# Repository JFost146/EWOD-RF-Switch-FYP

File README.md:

# Final Year Project  
## MEng Electrical and Electronic Engineering  
### Jack Foster — University of Birmingham

This repository contains the work completed for my final year MEng project at the University of Birmingham.

The project focuses on the development of an **electrowetting-on-dielectric (EWOD) circuit** designed to actuate a liquid droplet into a waveguide channel, where the liquid acts as part of an **RF switch**.

---

## Licence

This project is released under the **GNU General Public License v3.0**.

You are free to use, modify, and distribute the software and associated project files under the terms of the GPLv3. Any redistributed or modified versions must also comply with the GPLv3 terms.

A full copy of the licence is provided in the [`LICENSE`](license.txt) file.

Parts of this project are derived from or inspired by the GaudiLabs OpenDrop project and Nick de Smith’s Nixie high-voltage switching PSU. Please refer to the acknowledgements section for the original sources.

---

## Project Overview

The repository includes:

- KiCad circuit schematics and PCB design files
- Electrode board designs for EWOD testing
- Arduino-based control software
- RF switch simulation and measurement results
- Supporting notes and design references

---

## Circuit Basics

The `Circuit` folder contains the **KiCad 9.0** schematics, footprints, and manufacturing files used for the PCB.

The boards used in the project were manufactured by **JLCPCB** at approximately **£30 per board**. These boards used **ENIG plating** to optimise coupling between electrodes for EWOD operation. However, the design would likely still work with the cheaper **HASL** finish.

---

## Microcontroller and Software

The circuit was tested using a **Seeed Studio XIAO nRF52840**:

[Seeed Studio XIAO nRF52840 Documentation](https://wiki.seeedstudio.com/XIAO_BLE/)

The board should also be compatible with other microcontroller boards, as the controllable components operate using:

- `3V3`
- Clock signal
- Latch / chip-select signal

The controllable components are:

- Digital potentiometer
- High-voltage switch controller

The control code is written for **Arduino** and can be found in the `Software` folder.

---

## Board Setup and EWOD Testing

To use the board:

1. Snap off the electrode boards.
2. Solder all required components.
3. Connect an electrode board using fly-wires.
4. Add a hydrophobic oil layer to the electrodes.  
   - Silicone oil, **5 cSt**, is preferred.
5. Place a dielectric layer on top of the oil.  
   - Cling film can be used.
6. Add another oil layer on top of the dielectric.
7. Place the droplet above an electrode.
8. Observe the EWOD actuation.

---

## Notes and Testing Observations

- The potentiometer can be bypassed using the `R_pot_sub` resistor pads with either:
  - a `0 Ω` resistor, or
  - a solder bridge.

- Successful tests were proven at maximum voltage output, with the potentiometer set to `0 Ω`.

- EWOD actuation is likely to work at voltages of **200 V or higher**.

- The best EWOD results were achieved using the rectangular electrodes with droplets whose diameter was approximately equal to, or larger than, the width of one electrode.

- The board design is derived from the GaudiLabs OpenDrop board:  
  [GaudiLabs OpenDrop](https://www.gaudi.ch/OpenDrop/)

- The DC-DC converter design originates from Nick de Smith’s Nixie high-voltage switching PSU:  
  [Nick de Smith Nixie PSU](https://www.nick.desmith.net/Electronics/NixiePSU.html)

---

## Board Specifications

| Parameter | Value |
|---|---|
| Input voltage | 5 V |
| Input current at maximum output | 0.16 A |
| Theoretical input range | 4.5 V to 16 V |
| Electrode output voltage range | 50 V to 290 V |
| Electrode output current range | 2.3 µA to 13.2 µA |
| Number of electrode designs | 7 |
| Minimum tested standalone output from XIAO nRF52840 USB input  | 50 V |

---

## RF Switch Investigation

The `Liquid Switch Tests` results contain:

- CST simulation results
- VNA measurement results
- RF switch response data for different liquids

These results investigate the behaviour of an RF switch when closed using various liquid materials.

---

## Switch Link

Add switch link here.

---

## Acknowledgements

This project builds on open-source and publicly documented work from:

- [GaudiLabs OpenDrop](https://www.gaudi.ch/OpenDrop/)
- [Nick de Smith’s Nixie HV Switching PSU](https://www.nick.desmith.net/Electronics/NixiePSU.html)

---

## Author

**Jack Foster**  
MEng Electrical and Electronic Engineering  
University of Birmingham

## Project Supervisor

**Prof. Yi Wang**  
Department of Electronic, Electrical and Systems Engineering  
University of Birmingham

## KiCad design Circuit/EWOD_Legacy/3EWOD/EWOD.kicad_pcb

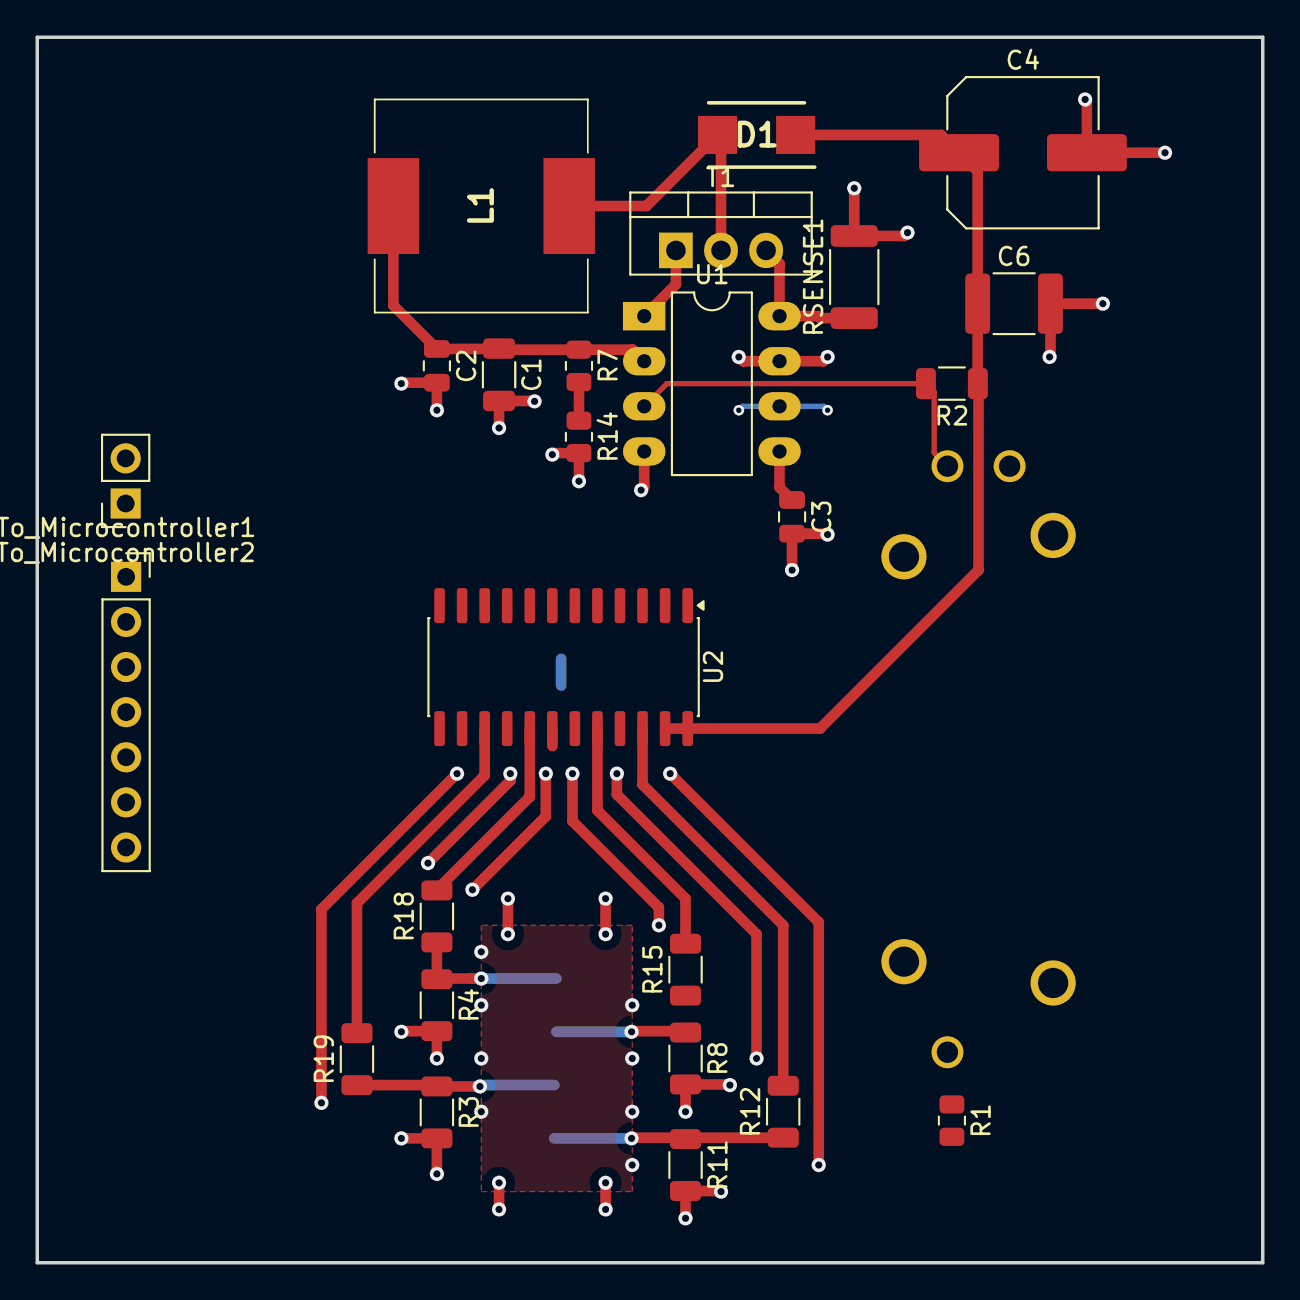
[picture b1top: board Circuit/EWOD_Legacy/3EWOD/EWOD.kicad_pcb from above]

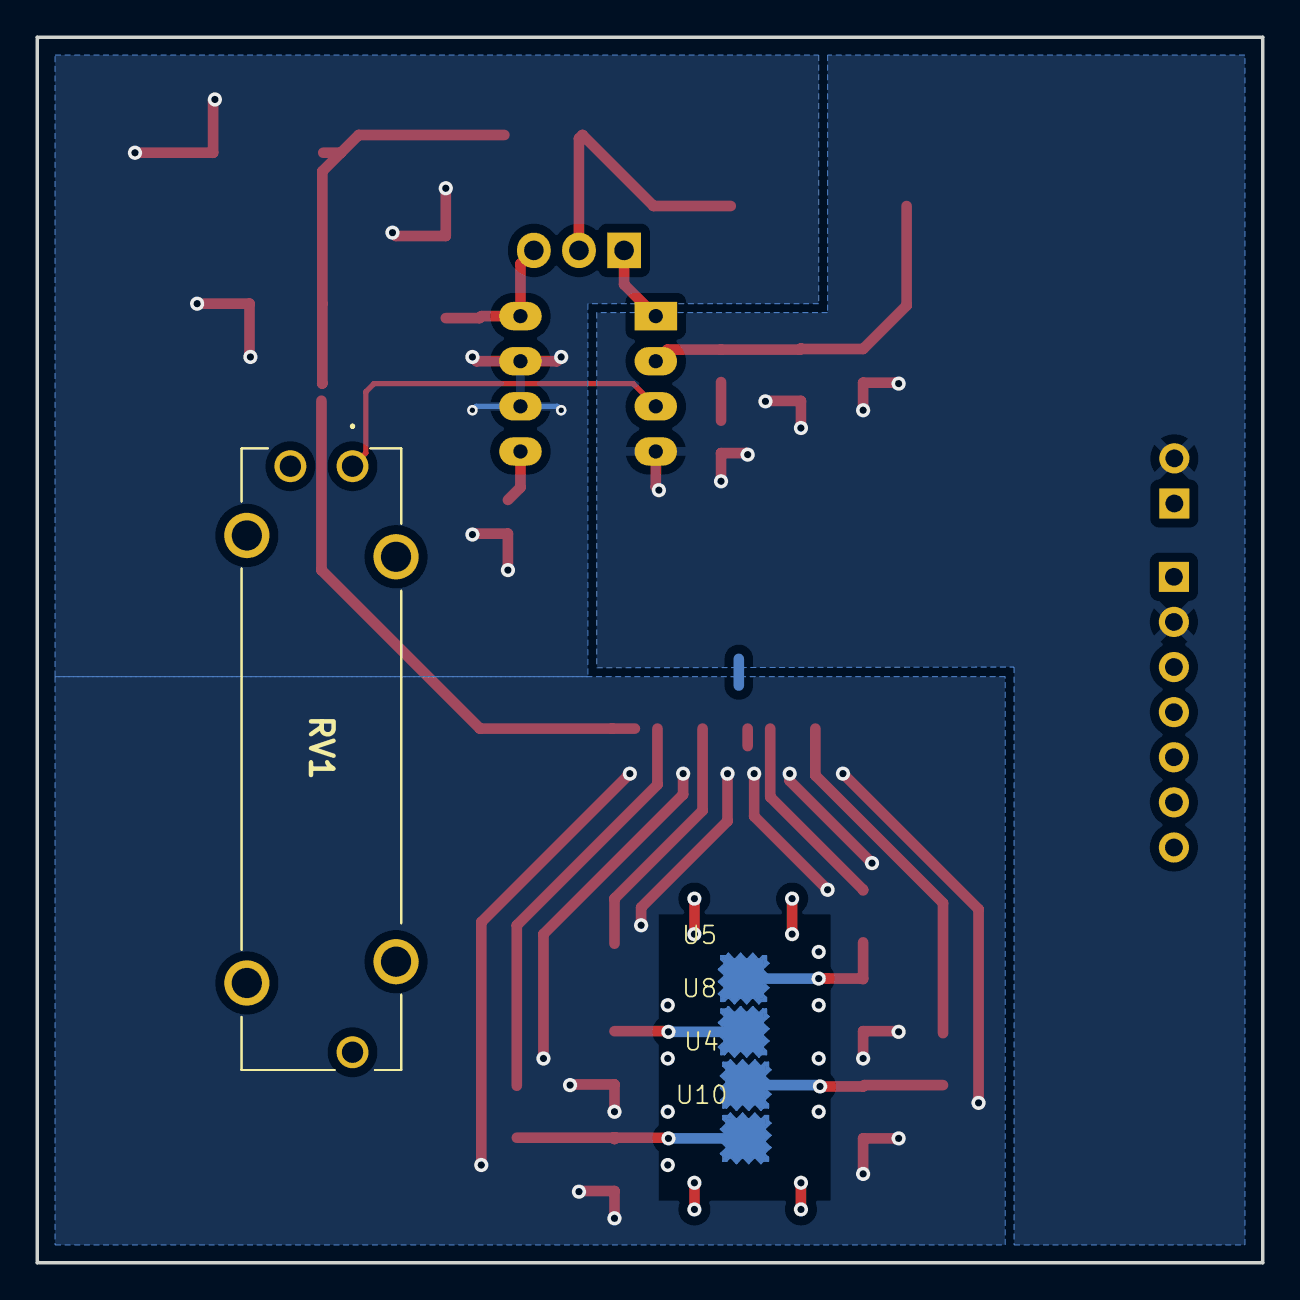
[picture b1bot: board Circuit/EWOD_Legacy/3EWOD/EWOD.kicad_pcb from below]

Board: 2 copper layers, 69.0 x 69.0 mm, 30 parts (5 on the bottom side), 24 nets.

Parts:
C1: 100uF, 6.3V; C_1206_3216Metric
C2, C3: 100nF; C_0805_2012Metric
C4: 4u7, 250V; C_Elec_8x10.2
C6: 100nF, 250V; C_1812_4532Metric
D1: ES2F; DIOM5436X244N
L1: 100uH; CDRH125101MC
R1: ak; R_0805_2012Metric
R2: 1M5; R_1206_3216Metric
R3, R4, R8, R11: 22M; R_1206_3216Metric
R7: 6.8k; R_0805_2012Metric
R12, R15, R18, R19: 200; R_1206_3216Metric
R14: 10k; R_0805_2012Metric
RSENSE1: 0R1; R_2010_5025Metric
RV1: R_Potentiometer; PTA20432015CPB503
T1: TK560P60Y; TO-220-3_Vertical
To_Microcontroller1: Conn_01x07; PinSocket_1x07_P2.54mm_Vertical
To_Microcontroller2: Conn_01x07; PinSocket_1x02_P2.54mm_Vertical
U1: MAX1771ESA; PowerIntegrations_PDIP-8
U2: HV513; SO-24_5.3x15mm_P1.27mm
U4: Electrode 2; Electrode
U5: Electrode 3; Electrode
U8: Electrode 6; Electrode
U10: Electrode 8; Electrode

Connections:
GND: C1.2, C2.2, C3.2, C4.2, C6.2, R1.2, R3.2, R4.2, R8.2, R11.2, R14.2, RSENSE1.2, To_Microcontroller1.2, To_Microcontroller2.2, U1.4 (SHDN), U1.6 (AGND), U1.7 (GND), U2.11 (LVGND), U2.13 (HVGND), U2.14 (HVGND)
unnamed: R1.1, RV1.3
unnamed: R11.1, R12.1, U10.1
unnamed: R8.1, R15.1, U8.1
unnamed: R4.1, R18.1, U5.1
unnamed: R3.1, R19.1, U4.1
unnamed: D1.2, L1.2, T1.2 (D)
unnamed: T1.1 (G), U1.1 (EXT)
unnamed: RSENSE1.1, T1.3 (S), U1.8 (CS)
unnamed: To_Microcontroller1.1, U2.2 (VDD_logic_supply)
unnamed: To_Microcontroller1.3, U2.4 (BL)
unnamed: To_Microcontroller1.4, U2.5 (POL)
unnamed: To_Microcontroller1.5, U2.6 (CLK)
unnamed: To_Microcontroller1.6, U2.7 (LE)
unnamed: To_Microcontroller1.7, U2.10 (DIN)
unnamed: R2.2, RV1.1, U1.3 (FB)
unnamed: C3.1, U1.5 (REF)
unnamed: C1.1, C2.1, L1.1, R7.1, U1.2 (VCC)
unnamed: R19.2, U2.15 (HVOUT1)
unnamed: R18.2, U2.17 (HVOUT3)
unnamed: R15.2, U2.20 (HVOUT6)
unnamed: R12.2, U2.22 (HVOUT8)
V_HV: C4.1, C6.1, D1.1, R2.1, U2.23 (HVpp), U2.24 (HVpp)
V_In_SENS: R7.2, R14.1

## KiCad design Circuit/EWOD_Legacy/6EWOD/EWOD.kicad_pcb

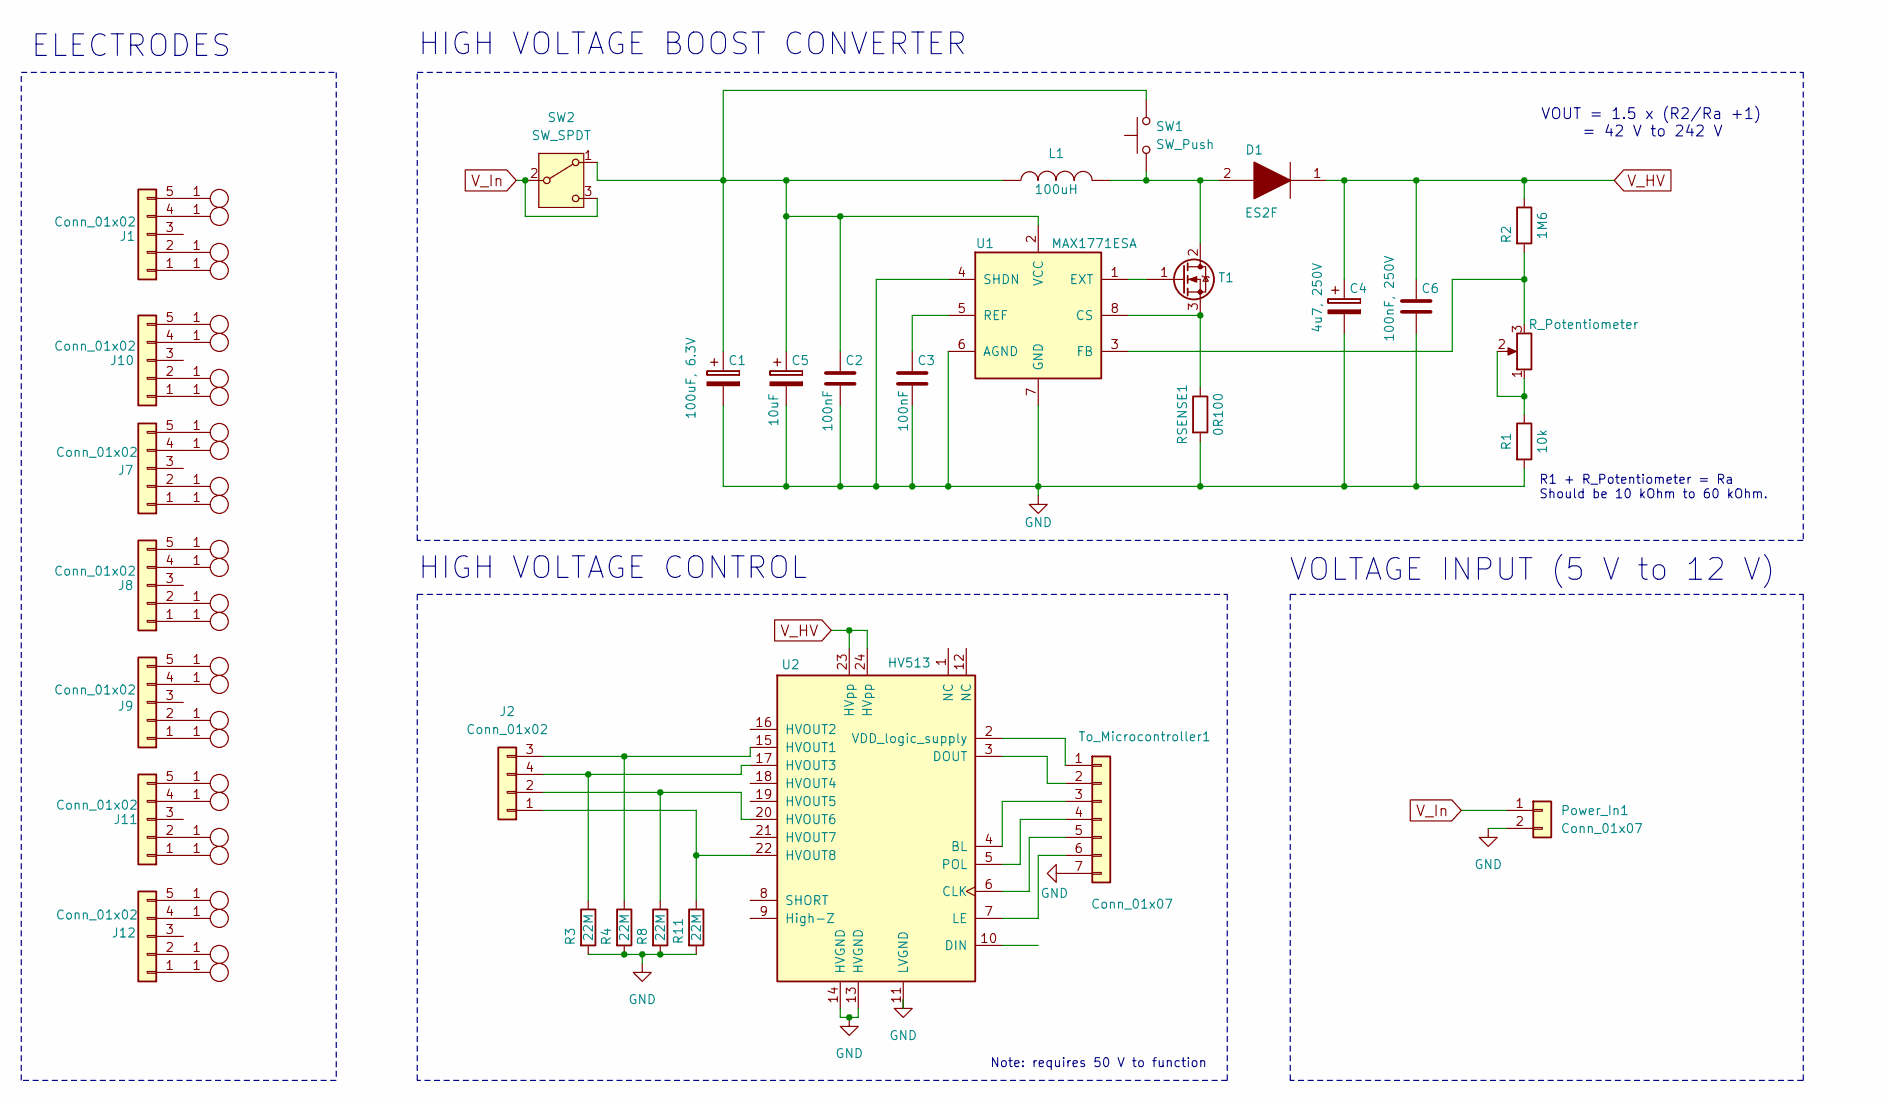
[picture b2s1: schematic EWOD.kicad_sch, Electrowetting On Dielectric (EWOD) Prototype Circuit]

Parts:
C1: 100uF, 6.3V; CP_Elec_6.3x5.4_Nichicon
C2, C3: 100nF; C_0805_2012Metric
C4: 4u7, 250V; CP_Elec_10x10.5
C5: 10uF; C_1206_3216Metric
C6: 100nF, 250V; C_1812_4532Metric
D1: ES2F; DIOM5436X244N; Manufacturer_Part_Number ES2F-E3/52T; Mouser Part Number 625-ES2F-E3
J1, J7, J8, J9, J10, J11, J12: Conn_01x02; Zhaoxing_VH_ZX-VH3.96-5PLT_1x05-1MP_P3.96mm_Vertical_0
J2: Conn_01x02; PinSocket_1x04_P2.54mm_Vertical
L1: 100uH; CDRH125101MC
Power_In1: Conn_01x07; PinSocket_1x02_P2.54mm_Vertical
R1: 10k; R_0805_2012Metric
R2: 1M6; R_1206_3216Metric
R3, R4, R8, R11: 22M; R_1206_3216Metric
RSENSE1: 0R100; R_2010_5025Metric
RV1: R_Potentiometer; SOT-363_SC-70-6_Handsoldering
SW1: SW_Push
SW2: SW_SPDT; PinHeader_1x03_P2.54mm_Vertical
T1: TK560P60Y; TO-220-3_Vertical
To_Microcontroller1: Conn_01x07; PinSocket_1x07_P2.54mm_Vertical
U1: MAX1771ESA; PowerIntegrations_PDIP-8
U2: HV513; SOP-24_7.5x15.4mm_P1.27mm
U4: Electrode 2; Electrode
U5: Electrode 3; Electrode
U8: Electrode 6; Electrode
U10: Electrode 8; Electrode
U11, U12, U13, U14: Electrode 2; Electrode_2_1
U15, U16, U17, U18: Electrode 2; Electrode_3
U19, U20, U21, U22: Electrode 2; Electrode_4
U23, U24, U25, U26: Electrode 2; Electrode_2
U27, U28, U29, U30: Electrode 2; Electrode_5
U31, U32, U33, U34: Electrode 2; Electrode_6

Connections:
GND: C1.2, C2.2, C3.2, C4.2, C5.2, C6.2, Power_In1.2, R1.2, R3.2, R4.2, R8.2, R11.2, RSENSE1.2, To_Microcontroller1.7, U1.4 (SHDN), U1.6 (AGND), U1.7 (GND), U2.11 (LVGND), U2.13 (HVGND), U2.14 (HVGND)
unnamed: J1.1, U10.1
unnamed: J1.2, U8.1
unnamed: J1.4, U5.1
unnamed: J1.5, U4.1
unnamed: J2.1, R11.1, U2.22 (HVOUT8)
unnamed: J2.2, R8.1, U2.20 (HVOUT6)
unnamed: J2.4 (Pin_3), R3.1, U2.17 (HVOUT3)
unnamed: J2.3 (Pin_4), R4.1, U2.15 (HVOUT1)
unnamed: J7.1, U14.1
unnamed: J7.2, U13.1
unnamed: J7.4, U12.1
unnamed: J7.5, U11.1
unnamed: J8.1, U18.1
unnamed: J8.2, U17.1
unnamed: J8.4, U16.1
unnamed: J8.5, U15.1
unnamed: J9.1, U22.1
unnamed: J9.2, U21.1
unnamed: J9.4, U20.1
unnamed: J9.5, U19.1
unnamed: J10.1, U26.1
unnamed: J10.2, U25.1
unnamed: J10.4, U24.1
unnamed: J10.5, U23.1
unnamed: J11.1, U30.1
unnamed: J11.2, U29.1
unnamed: J11.4, U28.1
unnamed: J11.5, U27.1
unnamed: J12.1, U34.1
unnamed: J12.2, U33.1
unnamed: J12.4, U32.1
unnamed: J12.5, U31.1
unnamed: R1.1, RV1.1, RV1.2
unnamed: C1.1, C2.1, C5.1, L1.1, SW1.2, SW2.1 (A), U1.2 (VCC)
unnamed: D1.2, L1.2, SW1.1, T1.2 (D)
unnamed: T1.1 (G), U1.1 (EXT)
unnamed: RSENSE1.1, T1.3 (S), U1.8 (CS)
unnamed: To_Microcontroller1.1, U2.2 (VDD_logic_supply)
unnamed: To_Microcontroller1.2, U2.3 (DOUT)
unnamed: To_Microcontroller1.3, U2.4 (BL)
unnamed: To_Microcontroller1.4, U2.5 (POL)
unnamed: To_Microcontroller1.5, U2.6 (CLK)
unnamed: To_Microcontroller1.6, U2.7 (LE)
unnamed: R2.2, RV1.3, U1.3 (FB)
unnamed: C3.1, U1.5 (REF)
V_HV: C4.1, C6.1, D1.1, R2.1, U2.23 (HVpp), U2.24 (HVpp)
V_In: Power_In1.1, SW2.2 (B), SW2.3 (C)

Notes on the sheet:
HIGH VOLTAGE CONTROL
Note: requires 50 V to function
ELECTRODES
HIGH VOLTAGE BOOST CONVERTER
R1 + R_Potentiometer = Ra Should be 10 kOhm to 60 kOhm.
VOUT = 1.5 x (R2/Ra +1) = 42 V to 242 V
VOLTAGE INPUT (5 V to 12 V)

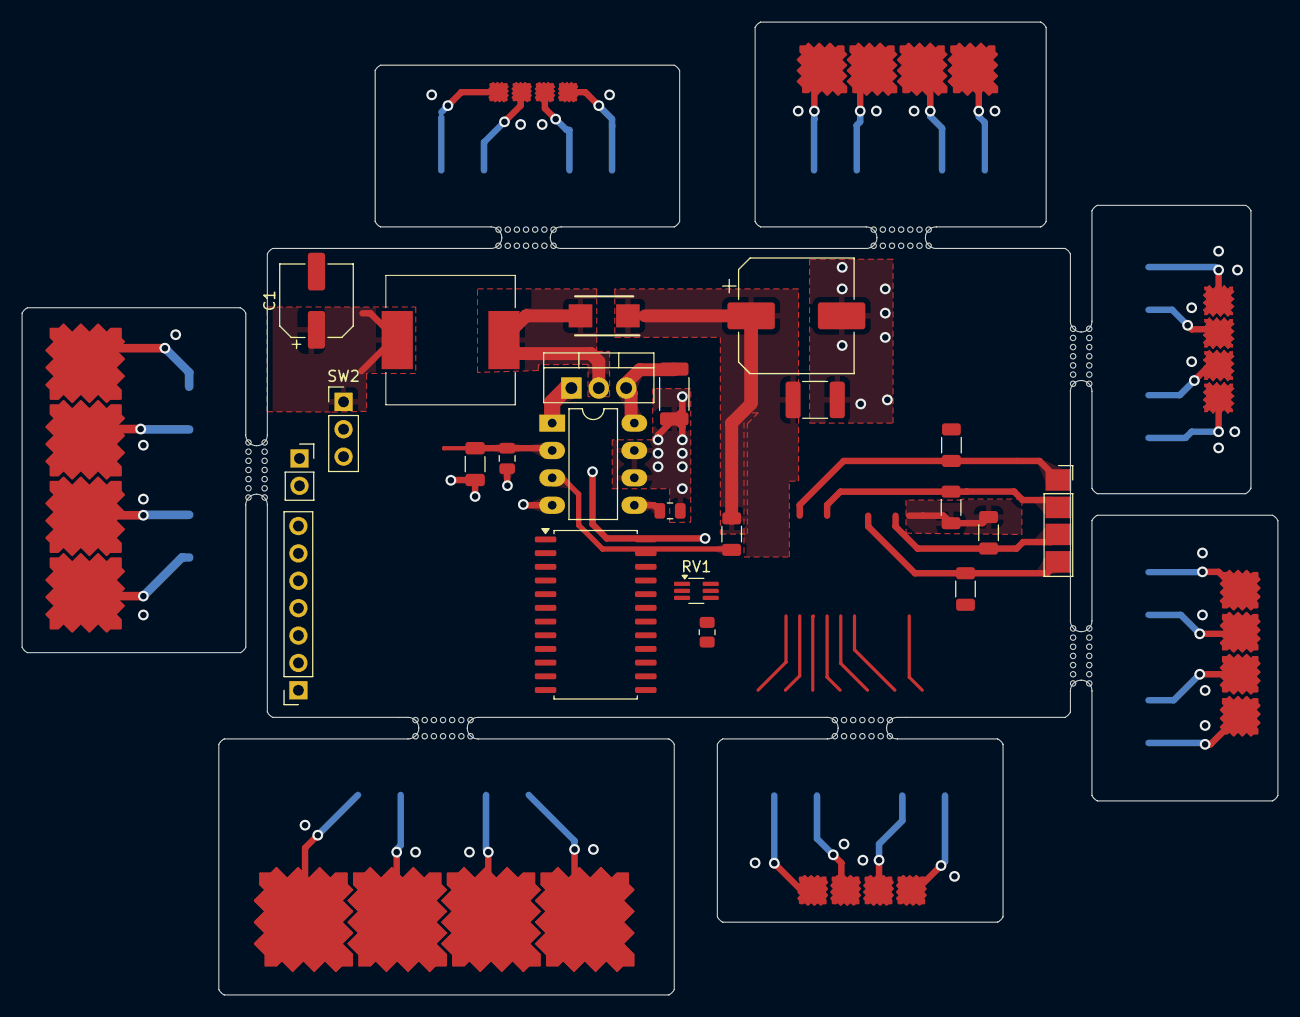
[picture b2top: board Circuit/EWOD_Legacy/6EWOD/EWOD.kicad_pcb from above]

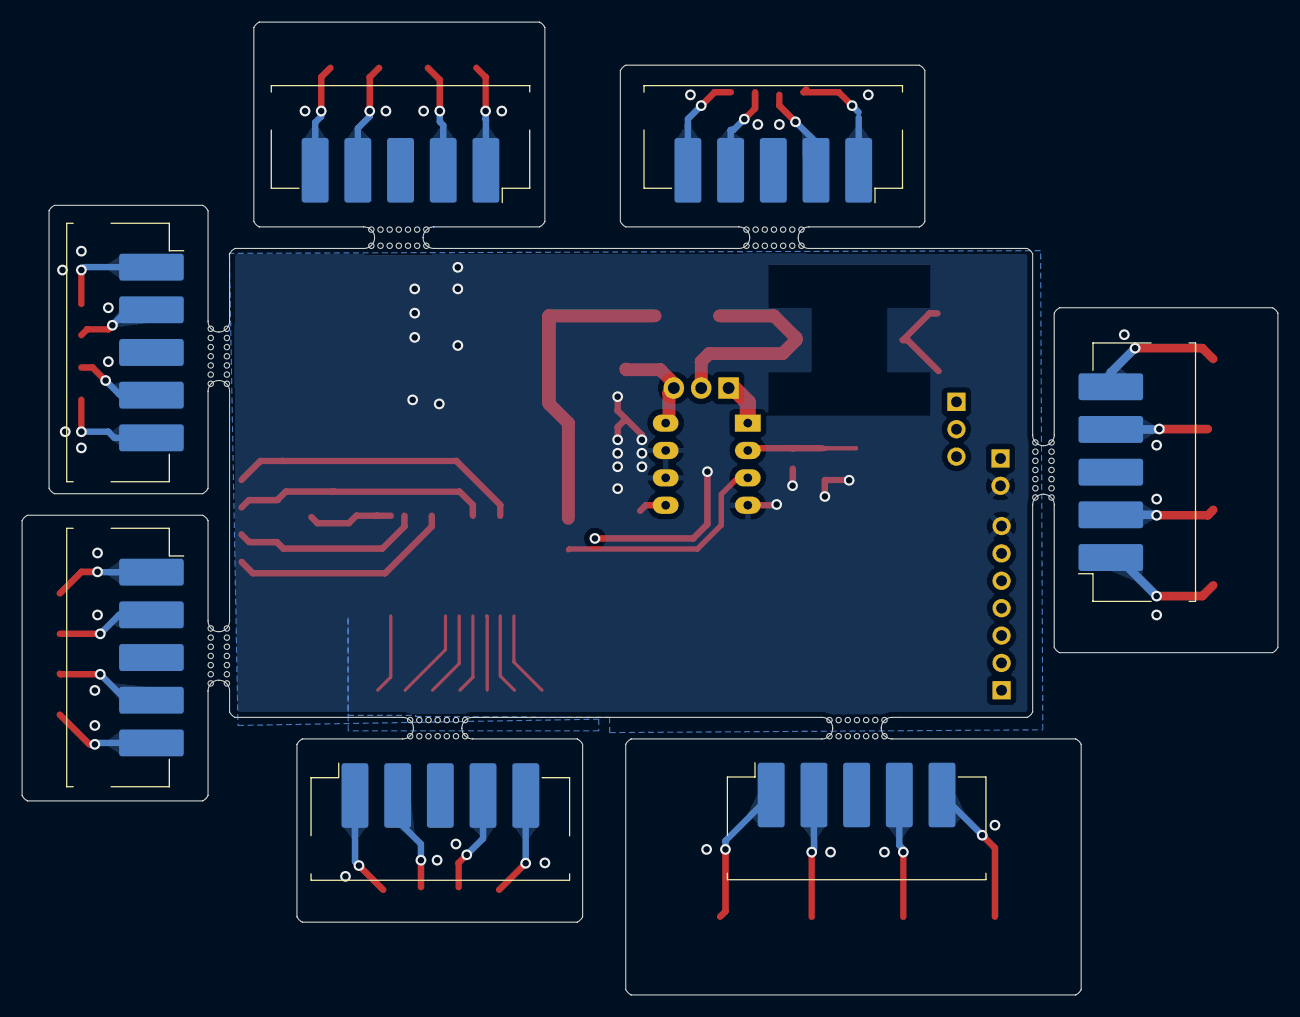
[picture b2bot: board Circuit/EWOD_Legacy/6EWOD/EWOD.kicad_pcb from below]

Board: 2 copper layers, 116.5 x 90.2 mm, 72 parts (7 on the bottom side), 48 nets.

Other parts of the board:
J3, J3#2, J3#3, J3#4, J3#5, J3#6, J3#7, J3#8, J3#9, J3#10, J5, J5#2, J5#3, J5#4: Screw_Terminal_01x01; MouseBite-Part_2.0x4.5mm_outset_D0.5mm_P0.85mm_7h

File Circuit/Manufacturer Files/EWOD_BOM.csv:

Comment,Qty,Designator,Footprint,LCSC Part Number,,Manufacturer UK,Manufacturer Part Number 
0 Ohms,1,R_pot_sub1,-,-,,,
100nF,2,"C2,C3",0805,C38141,,Digikey,478-KGM21NR71H104KTCT-ND
10uF,1,C5,1206,C1849,,Digikey,CL31A106KBHNNNE
100uF,1,C1,Capacitor_SMD:CP_Elec_6.3x5.4_Nichicon,C2161820,,Digikey,875105344010
100uH,1,L1,CDRH125101MC,C212268,,Digikey,CDRH125/LDNP-101MC
8k,1,R1,0805,C413197,,Digikey,P0805Z8001FNT
10k,1,R5,0805,C22356686,,Digikey,CRCW080510K0FKEA
"22M, 250 V",4,"R3,R4,R8,R11",1206,C41755,,Digikey,RMCF1206JT22M0
"0R100, 1.5 A",1,RSENSE1,2010,C159215,,Digikey,WSL2010R1000FEA18
"100nF, 250V",1,C6,1812,C304034,,Digikey,CC1812KKX7RYBB104
"1M6, 250 V",1,R2,0805,C723463,,Digikey,KTR10EZPF1604
"4u7, 250V",1,C4,Capacitor_SMD:CP_Elec_10x10.5,C5549292,,Digikey,AEH10104R7M250R
Conn_01x02,7,"J1,J2,J8,J9,J10,J11,J12",-,-,,,
Conn_01x02,1,J7,-,-,,,
Conn_01x07,2,"Power_In1,Power_In2",-,-,,,
Conn_01x08,1,Microcontroller1,-,-,,,
Electrode 2,5,"U4,U11,U12,U13,U14",-,-,,,
Electrode 2,4,"U9,U23,U24,U25",-,-,,,
Electrode 2,4,"U15,U16,U17,U18",-,-,,,
Electrode 2,4,"U19,U20,U21,U22",-,-,,,
Electrode 2,4,"U27,U28,U29,U30",-,-,,,
Electrode 2,4,"U31,U32,U33,U34",-,-,,,
Electrode 3,1,U5,-,-,,,
Electrode 6,1,U8,-,-,,,
Electrode 8,1,U10,-,-,,,
"Diode ES2F, 300 V 2 A",1,D1,DIOM5436X244N,"C222525
",,Mouser,625-ES2F-E3
Ground Ref,1,U7,-,-,,,
HV513,1,U2,Package_SO:SOP-24_7.5x15.4mm_P1.27mm,C631624,,Digikey,HV513WG-G
MAX1771ESA,1,U1,PowerIntegrations_PDIP-8,C3191535,,RS,MAX1771CPA
MCP41050,1,U26,Package_SO:SOIC-8_3.9x4.9mm_P1.27mm,C623335,,Digikey,MCP41050T-I/SN
MountingHole,14,"H8,H9,H10,H11,H12,H13,H14,H15,H16,H17,H18,H19,H20,H21",-,-,,,
MouseBites,7,"H1,H2,H3,H4,H5,H6,H7",-,-,,,
On Pad,1,U6,-,-,,,
Power Pad,1,U3,-,-,,,
SW_SPDT,1,SW2,-,-,,,
Test Pad,1,U35,-,-,,,
TK560P60Y,1,T1,Package_TO_SOT_THT:TO-220-3_Vertical,C469331,,Digikey,IRF644PBF-ND

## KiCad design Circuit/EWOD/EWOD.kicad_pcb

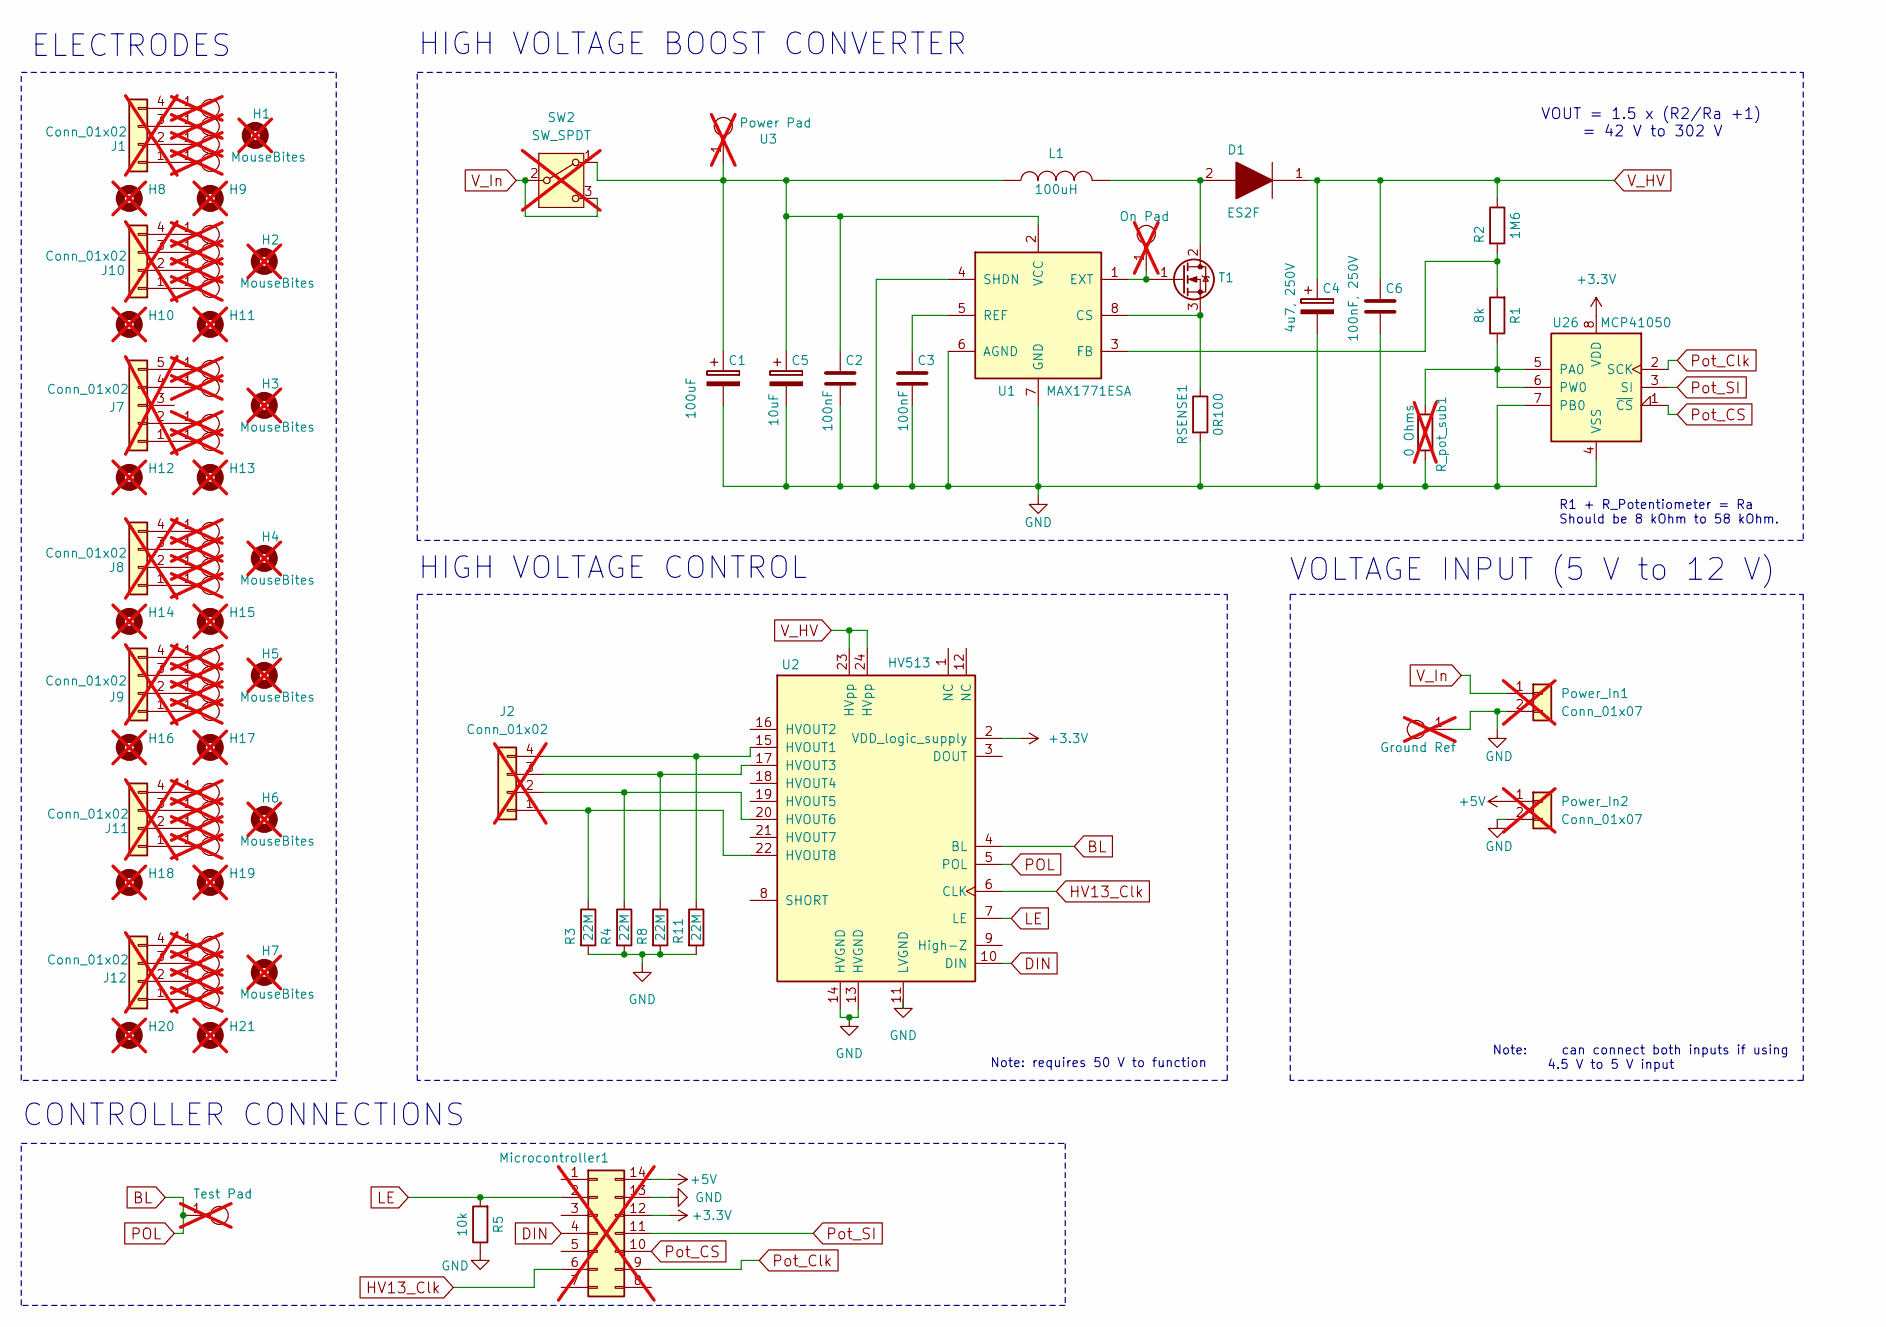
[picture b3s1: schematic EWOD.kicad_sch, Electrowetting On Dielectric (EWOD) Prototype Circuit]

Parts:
C1: 100uF; CP_Elec_6.3x5.4_Nichicon; Manufacturer_Part_Number 875105344010
C2, C3: 100nF; C_0805_2012Metric; Manufacturer_Part_Number 478-KGM21NR71H104KTCT-ND
C4: 4u7, 250V; CP_Elec_10x10.5; Manufacturer_Part_Number AEH10104R7M250R
C5: 10uF; C_1206_3216Metric; Manufacturer_Part_Number CL31A106KBHNNNE
C6: 100nF, 250V; C_1812_4532Metric; Manufacturer_Part_Number CC1812KKX7RYBB104
D1: ES2F; DIOM5436X244N; Manufacturer_Part_Number 625-ES2F-E3; Mouser Part Number 625-ES2F-E3
H1, H2, H3, H4, H5, H6, H7: MouseBites; Mousebites; not fitted
H8, H9, H10, H11, H12, H13, H14, H15, H16, H17, H18, H19, H20, H21: MountingHole; MountingHole_3.2mm_M3; not fitted
J1, J2, J8, J9, J10, J11, J12: Conn_01x02; PinSocket_1x04_P2.54mm_Vertical; not fitted
J7: Conn_01x02; PinHeader_1x05_P2.54mm_Vertical; not fitted
L1: 100uH; CDRH125101MC; Manufacturer_Part_Number CDRH125/LDNP-101MC
Microcontroller1: Conn_01x08; XIAO-nRF52840-DIP; not fitted
Power_In1, Power_In2: Conn_01x07; PinSocket_1x02_P2.54mm_Vertical; not fitted
R1: 8k; R_0805_2012Metric; Manufacturer_Part_Number P0805Z8001FNT
R2: 1M6; R_0805_2012Metric_Pad1.20x1.40mm_HandSolder; Manufacturer_Part_Number KTR10EZPF1604
R3, R4, R8, R11: 22M; R_1206_3216Metric; Manufacturer_Part_Number RMCF1206JT22M0
R5: 10k; R_0805_2012Metric; Manufacturer_Part_Number CRCW080510K0FKEA
RSENSE1: 0R100; R_2010_5025Metric; Manufacturer_Part_Number WSL2010R1000FEA18
R_pot_sub1: 0 Ohms; R_0805_2012Metric; not fitted
SW2: SW_SPDT; PinHeader_1x03_P2.54mm_Vertical; not fitted
T1: TK560P60Y; TO-220-3_Vertical; Manufacturer_Part_Number IRF644PBF-ND
U1: MAX1771ESA; PowerIntegrations_PDIP-8; Manufacturer_Part_Number MAX1771CPA
U2: HV513; SOP-24_7.5x15.4mm_P1.27mm; Manufacturer_Part_Number HV513WG-G
U3: Power Pad; TestPoint_Pad_D2.0mm; not fitted
U4, U11, U12, U13, U14: Electrode 2; Electrode; not fitted
U5: Electrode 3; Electrode; not fitted
U6: On Pad; TestPoint_Pad_D2.0mm; not fitted
U7: Ground Ref; TestPoint_Pad_D2.0mm; not fitted
U8: Electrode 6; Electrode; not fitted
U9, U23, U24, U25: Electrode 2; Electrode_6_2; not fitted
U10: Electrode 8; Electrode; not fitted
U15, U16, U17, U18: Electrode 2; Electrode_3; not fitted
U19, U20, U21, U22: Electrode 2; Electrode_4; not fitted
U26: MCP41050; SOIC-8_3.9x4.9mm_P1.27mm; Manufacturer_Part_Number MCP41050T-I/SN
U27, U28, U29, U30: Electrode 2; Electrode_5; not fitted
U31, U32, U33, U34: Electrode 2; Electrode_6; not fitted
U35: Test Pad; TestPoint_Pad_D3.0mm; not fitted

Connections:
+3.3V: Microcontroller1.12, U2.2 (VDD_logic_supply), U26.8 (VDD)
+5V: Microcontroller1.14, Power_In2.1
BL: U2.4 (BL), U2.5 (POL), U35.1
DIN: Microcontroller1.4, U2.10 (DIN)
GND: C1.2, C2.2, C3.2, C4.2, C5.2, C6.2, Microcontroller1.13, Power_In1.2, Power_In2.2, R3.2, R4.2, R5.1, R8.2, R11.2, RSENSE1.2, R_pot_sub1.2, U1.4 (SHDN), U1.6 (AGND), U1.7 (GND), U2.11 (LVGND), U2.13 (HVGND), U2.14 (HVGND), U7.1, U26.4 (VSS), U26.7 (PB0)
HV13_Clk: Microcontroller1.6, U2.6 (CLK)
LE: Microcontroller1.2, R5.2, U2.7 (LE)
unnamed: J1.1, U10.1
unnamed: J1.2, U8.1
unnamed: J1.3, U5.1
unnamed: J1.4, U4.1
unnamed: J2.1, R3.1, U2.22 (HVOUT8)
unnamed: J2.2, R4.1, U2.20 (HVOUT6)
unnamed: J2.3, R8.1, U2.17 (HVOUT3)
unnamed: J2.4, R11.1, U2.15 (HVOUT1)
unnamed: J7.1, U14.1
unnamed: J7.2, U13.1
unnamed: J7.4, U12.1
unnamed: J7.5, U11.1
unnamed: J8.1, U18.1
unnamed: J8.2, U17.1
unnamed: J8.3, U16.1
unnamed: J8.4, U15.1
unnamed: J9.1, U22.1
unnamed: J9.2, U21.1
unnamed: J9.3, U20.1
unnamed: J9.4, U19.1
unnamed: J10.1, U25.1
unnamed: J10.2, U24.1
unnamed: J10.3, U9.1
unnamed: J10.4, U23.1
unnamed: J11.1, U30.1
unnamed: J11.2, U29.1
unnamed: J11.3, U28.1
unnamed: J11.4, U27.1
unnamed: J12.1, U34.1
unnamed: J12.2, U33.1
unnamed: J12.3, U32.1
unnamed: J12.4, U31.1
unnamed: C1.1, C2.1, C5.1, L1.1, SW2.1 (A), U1.2 (VCC), U3.1
unnamed: D1.2, L1.2, T1.2 (D)
unnamed: T1.1 (G), U1.1 (EXT), U6.1
unnamed: RSENSE1.1, T1.3 (S), U1.8 (CS)
unnamed: R1.2, R2.2, U1.3 (FB)
unnamed: C3.1, U1.5 (REF)
unnamed: R1.1, R_pot_sub1.1, U26.5 (PA0), U26.6 (PW0)
Pot_CS: Microcontroller1.10, U26.1 (~CS)
Pot_Clk: Microcontroller1.9, U26.2 (SCK)
Pot_SI: Microcontroller1.11, U26.3 (SI)
V_HV: C4.1, C6.1, D1.1, R2.1, U2.23 (HVpp), U2.24 (HVpp)
V_In: Power_In1.1, SW2.2 (B), SW2.3 (C)

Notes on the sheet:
HIGH VOLTAGE CONTROL
Note: requires 50 V to function
ELECTRODES
HIGH VOLTAGE BOOST CONVERTER
Note: can connect both inputs if using 4.5 V to 5 V input
R1 + R_Potentiometer = Ra Should be 8 kOhm to 58 kOhm.
VOUT = 1.5 x (R2/Ra +1) = 42 V to 302 V
CONTROLLER CONNECTIONS
VOLTAGE INPUT (5 V to 12 V)

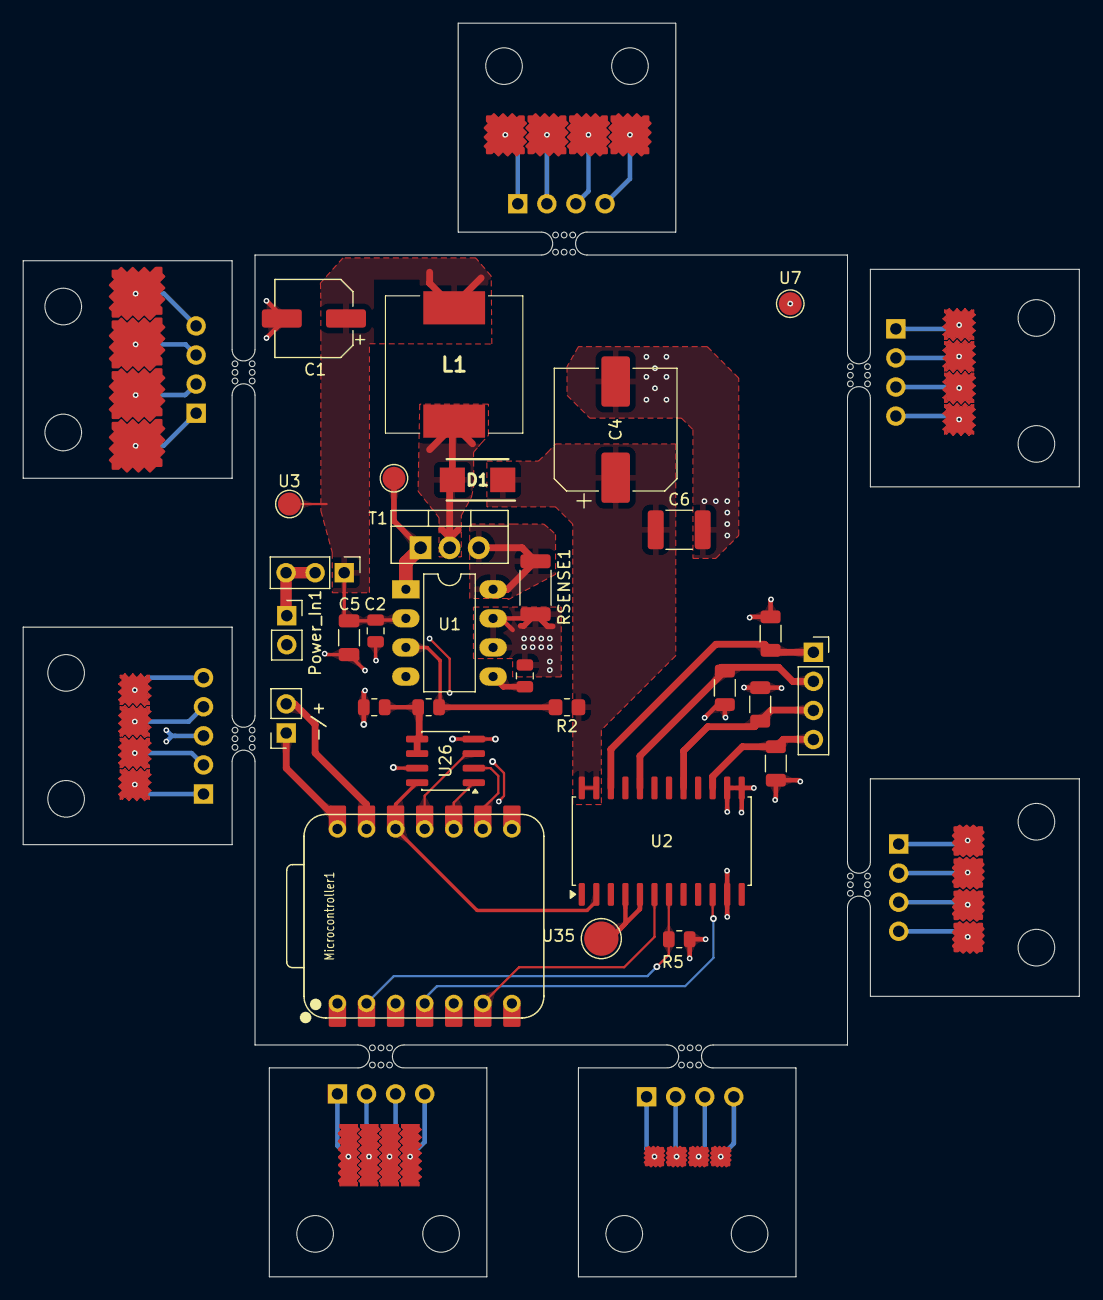
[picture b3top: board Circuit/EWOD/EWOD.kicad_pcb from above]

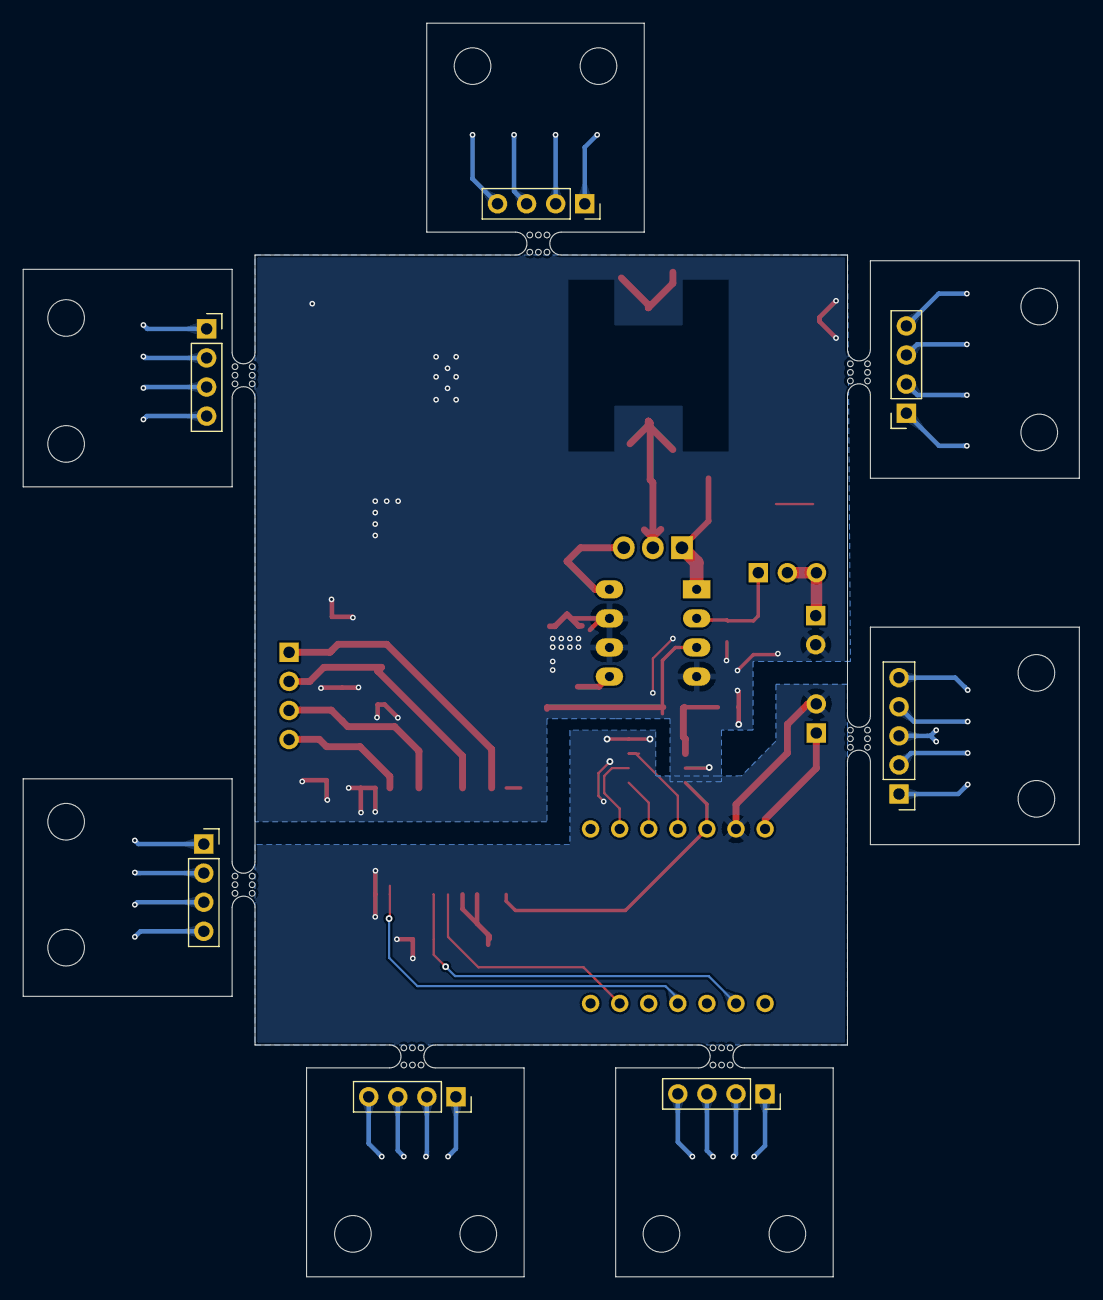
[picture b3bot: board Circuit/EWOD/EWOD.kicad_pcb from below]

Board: 2 copper layers, 92.2 x 109.4 mm, 86 parts (7 on the bottom side), 51 nets.

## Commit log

2026-04-16 Circuit files and some test results
2026-04-16 Software for EWOD Circuit with added Helper Functions
2026-04-16 README Update
2026-05-08 General tidying: Added code from the current printed EWOD circuit board in case further work is done with it. Added license, updated some test files, updated the READ.me, and added the CST switch fil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
2026-05-08 READ.me Change
